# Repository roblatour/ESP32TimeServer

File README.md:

# ESP32 NTP and PTP Stratum 1 Time Server (version 4.0)

An ESP32 NTP and PTP Stratum 1 Time Server for home networks

---

## Overview

This project was born with a simple goal: create a low-budget, **Stratum 1
Network Time Protocol (NTP) time server** with no need for periodic
Linux OS updates. Rather just set it up and let it do its job.

More recently Precision Time Protocol (PTP) support has been added.

ESP32TimeServer can serve NTP, PTP Layer 2 PTP, and PTP Layer 3
UDP Multicast, individually or in any combination.

ESP32TimeServer uses a **GNSS (North America & Europe) receiver** as its time source, 
making it a true Stratum 1 server — meaning it gets its time directly from satellites
rather than from another server. Every device on your home network can then
synchronize to it for highly accurate local time.

ESP32TimeServer supports Waveshare ESP32-P4 Ethernet dev boards and the 
ESP32-S31 Function CoreBoard-1.

---

## What's New

**Version 4** brings the following changes:

- Support for the ESP32-S31 (preview) chip which provides for Gigabit Ethernet.
  Performance of the ESP32-S31 (preview) chip surpasses  the ESP32-P4 rel 1.3 chip,
  but is below the ESP32-P4 rel 3.2 chip. 
- Added Precision Time Protocol (PTP) support. The server can now operate
  as an NTP, PTP Layer 2 (L2), PTP Layer 3 (L3) UDP Multicast, or any and all 
  combinations simultaneously.
- Both the NTP and PTP L2 protocols support operation with or without 
  authentication. NTP and PTP L2 have independent mixed/authenticated-only 
  policy settings, each defaulting to mixed mode. 
  Additional notes: 
  1. PTP servers sync time with their clients with a degree of precision measured in 
  Nanoseconds (ns) as opposed to a Network Time Protocol (NTP) server with a degree of
  precision measured in Microseconds (µs) (1 second = 1 million µs = 1 billion ns).
  2. PTP servers and their followers, will not work in virtual environments nor 
  across router (OPNSense/pfSense) interfaces - they do however work
  within the same interface. 
  3. Linux chrony implementations provides for NTP time and or 
  PTP L2 time with a fall back to NTP time.  Windows implementations
  provide for either NTP time or PTP L3 time but with not
  PTP L3 with NTP fallback.
- added/updated the following companion programs:

  (added) ESP32PTPL2Follower ( https://github.com/roblatour/ESP32PTPL2Follower )
  an example PTP L2 Follower for the ESP32-P4 and ESP32-S31 platforms

  (added) ESP32PTPL3Follower ( https://github.com/roblatour/ESP32PTPL3Follower )
  an example PTP L3 UDP Multicast Follower for the ESP32-P4 and ESP32-S31 platforms
  
  (added) tools\configTimeSettings.ps1 a python script to automate the setup of native
  Windows w32time client for use with ESP32TimeServer in either NTP or PTP L3 UDP modes
    
  (updated) ESP32TimeServerTester ( https://github.com/roblatour/ESP32TimeServerTester )
  to test PTP L2 and L3 UDP Multicast servers 

- removed use of the Arduino Sparkfun GNSS library (adapting its needed code for use within 
  ESP-IDF) as well as the last vestiges of Arduino code.  This was done to support the
  ESP32-S31 chip which while supported in the ESP-IDF environment is 
  not supported in the Arduino environment (although may be in the future)
- added automated regression testing 
  for more information please see [here](./testing/README.md)
- updates to MQTT messaging for new PTP reporting and to provide for, in most cases, more saved 
  messages in memory when a TF card is not available
- updates to Home Assistant configurations for new PTP reporting
- added external TF card reader support for the ESP32-S31 as the Espressif Functional CoreBoard - 1
  does not have a built in TF card reader
- revised leap-second processing aligned to the CGPM's decision to do away with leap-second processing in May 2027 
  for more information please see [here](./misc/leap_second_handling.md)
- added read back confirmation of Ublox receiver going in to stationary mode 
- several other updates and improvements

**Version 3** further improvements:
- **NTPv4 Symmetric-key authentication** added for Windows 
  clients using Meinberg and Linux clients using chrony. 
- **WS2182** RGB LED support added.
- **Stationary GNSS mode** — with UBLOX compliant GNSS receivers the program enables
  stationary-mode for improved time reporting. 
- updated to use Espressif's Ethernet and OTE update (TCP 3232) processes in place of 
  the Arduino Ethernet and OTE update (UDP 3232) processes
- improved accuracy when using the ESP32-P4 release 3.0 or above chip

**Version 2** was a ground-up rewrite which came with a faster, more capable board 
support and a long list of accuracy, reliability, and convenience improvements over
version 1, including:

- **Higher accuracy, lower jitter** — full use of the GPS module's PPS
  (Pulse Per Second) pin disciplines the clock for sub-millisecond accuracy,
  with hardware time stamping and RFC 9769-compatible interleaved responses
  further reducing jitter for both NTPv3 and NTPv4 requests.
- **Faster, more modern hardware** — built around the WaveShare ESP32-P4-ETH
  (or the newer ESP32-P4-WIFI6-ETH), a significant step up from the
  ESP32-WROOM-32/32E used in v1.
- **Broader GNSS module support** — still works great with the recommended
  SparkFun MAX-M10S, but also supports lower-cost generic GNSS modules and now
  has experimental support for the GT-U16, which offers better reception than
  some competing receivers at the same or higher price points.
- **Wired firmware updates** — Over-the-Ethernet updates let you push
  new firmware directly from VS Code, with on-screen progress shown on the
  LCD, so you rarely need to plug in a cable after the first flash.
- **Handles more traffic** — greatly increased throughput and concurrent
  request handling, so the server keeps up even on busy networks.
- **IPv6 support** — the server now responds to NTP requests over IPv6 as
  well as IPv4.
- **Flexible networking** — set a custom MAC address or a static IP, instead
  of always relying on the device's default address and DHCP.
- **MAC address selection** — `MACAddress` is a base-MAC override and is applied
  before Ethernet starts. For PTP master selection, use the active six-byte
  address reported as `Active Ethernet MAC` at startup; the SDK may derive a
  different Ethernet source MAC from the base address.
- **Optional LCD support** — a 4x20 LCD screen was required in v1; 
  in v2 it's entirely optional, along with an optional up time / reset button.
- **Optional KY-016 RGB LED support added** — [here](misc/status_indicators.md)
  is how that is used.
- **Smart GNSS lock tracking** — improved satellite lock and PPS discipline
  tracking, with results correctly reported as Stratum 16 (undefined) if lock
  or discipline is temporarily lost, and automatic recovery once it's
  restored.
- **Quick restarts** — GPS module identity and baud rate are saved to
  non-volatile storage, so the server starts up quickly after the initial
  setup.
- **MQTT publishing** — optionally publish time server stats to an MQTT
  broker, with TF card support for queueing far more messages if the broker
  connection drops.
- **Home Assistant integration** — ready-made entity and dashboard setup
  instructions for pulling time server stats into Home Assistant.
- **Built-in self-test** — an optional startup health check lets the server
  verify its own core functionality every time it boots.
- **Testing tools and guidance** — instructions, tools, and links for
  measuring jitter, drift, RFC 9769 compliance, memory usage, and server
  performance under stress.
- **Updated 3D printed case** — enclosure files refreshed for the new
  WaveShare ESP32-P4-ETH board.

 **Version 1** described in detail [here](https://hackaday.io/project/189309-esp32-ntp-time-server-stratum-1) was built for Arduino / PlatformIO and remains available
 [here](https://github.com/roblatour/ESP32TimeServer/releases/tag/v1.0.0.0).
>
([Detailed release history](https://github.com/roblatour/ESP32TimeServer/releases))

---

## Hardware

| Qty | Item                                                                                                                                                                                                                                                                                                                                                                                                                                                                                                                                                                                                                                                                                                                                                                         |
| --- | ---------------------------------------------------------------------------------------------------------------------------------------------------------------------------------------------------------------------------------------------------------------------------------------------------------------------------------------------------------------------------------------------------------------------------------------------------------------------------------------------------------------------------------------------------------------------------------------------------------------------------------------------------------------------------------------------------------------------------------------------------------------------------- |
| 1   | WaveShare [ESP32-P4-ETH](https://www.waveshare.com/esp32-p4-eth.htm?sku=32086) or [ESP32-P4-WIFI6-ETH](https://www.waveshare.com/esp32-p4-wifi6-poe-eth.htm?sku=32832) development board (with or without optional PoE) <sup>1 2</sup>, or the experimental [ESP32-S31 Function CoreBoard-1](https://www.aliexpress.com/item/1005013174212520.html).                                                                                                                                                                                                                                                                                                                                                                                                                         |
| 1   | GPS/GNSS module Recommened: [SparkFun GNSS Receiver Breakout - MAX-M10S (Qwiic)](https://www.sparkfun.com/sparkfun-gnss-receiver-breakout-max-m10s-qwiic.html?affiliate_code=dW1O7LlPwh&referring_service=link) <sup>2</sup>.  Additionally, one project user reported using this [MAX-M10N board](https://canada.newark.com/mikroelektronika/mikroe-6786/add-on-brd-microbus-compatible/dp/09AN2199) just fine.  Beyond that, support for the [GT U16](https://www.aliexpress.com/item/1005008288311771.html) has been added in version 2.9 - this receiver offers superior reception when coupled with the right antenna (see notes below).  Additionally, while some lower-cost generic modules UBlox compliant receivers are supported, those without a PPS pin are not. |
| 1   | GPS/GNSS antenna with SMA connector ([SparkFun GPS/GNSS Magnetic Mount Antenna - 3m (SMA)](https://www.sparkfun.com/products/14986?affiliate_code=dW1O7LlPwh&referring_service=link)) <sup>2</sup>. Alternatively the GT U16 with an L1/L5 antenna offers superior reception.  However, in my testing I used the [3M SMA W70C](https://www.aliexpress.com/item/1005008421771962.html?spm=a2g0o.order_list.order_list_main.11.7a7f1802GCXbvZ) L1/L2/L5 antenna an [IPEX to SMA adapter](https://s.click.aliexpress.com/e/_c31hthKJ) and got very good results (I have the antenna bundled with the GT U16 (link above) on order and when I get it and test it I will update this page).                                                                                       |
| 1   | _(Optional)_ RGB LED: KY-016 ([AliExpress](https://s.click.aliexpress.com/e/_c3Jceyex)) or WS2812 ([AliExpress](https://s.click.aliexpress.com/e/_c3rjPVub)) with a 470&Omega; resistor and optional lens cap ([AliExpress](https://www.aliexpress.com/item/1005003854908953.html))                                                                                                                                                                                                                                                                                                                                                                                                                                                                                          |
| 1   | _(Optional)_ 4×20 I²C LCD display with HD44780 controller with PCF8574 I²C backpack ([AliExpress](https://www.aliexpress.com/item/1005006829045609.html)) <sup>2</sup>                                                                                                                                                                                                                                                                                                                                                                                                                                                                                                                                                                                                       |
| 1   | _(Optional)_ Momentary push button for displaying up time and triggering a reset ([AliExpress](https://s.click.aliexpress.com/e/_c4UbVuTN)) <sup>2</sup>                                                                                                                                                                                                                                                                                                                                                                                                                                                                                                                                                                                                                     |
| 1   | _(Optional)_ USB C extension cable (with right angle end) ([AliExpress](https://s.click.aliexpress.com/e/_c3C5c6Kx)) <sup>2</sup> + two M3*8                                                                                                                                                                                                                                                                                                                                                                                                                                                                                                                                                                                                                                 |
| 1   | _(Optional)_ TF Card Reader (only needed for the ESP32-S31 Functional Coreboard-1; the WaveShare ESP32-P4-ETH series boards have a built in TF Card Reader) ([AliExpress](https://s.click.aliexpress.com/e/_c34w6E9D))                                                                                                                                                                                                                                                                                                                                                                                                                                                                                                                                                       |
| 1   | _(Optional)_ TF Card, formatted as FAT32, if you're using MQTT and want a larger queue, kept through power loss, should broker communications be down                                                                                                                                                                                                                                                                                                                                                                                                                                                                                                                                                                                                                        |
| —   | Miscellaneous: Ethernet cable, [female dupont connection wires](https://s.click.aliexpress.com/e/_c3UwFX2R), small 4" .1" zip ties, solder <sup>2</sup>                                                                                                                                                                                                                                                                                                                                                                                                                                                                                                                                                                                                                      |
| —   | A PoE-capable switch, PoE injector, **or** USB-C power supply and USB-C cable                                                                                                                                                                                                                                                                                                                                                                                                                                                                                                                                                                                                                                                                                                |

> ⚠️ **WARNING — Do NOT power the ESP32-P4-POE-ETH or the ESP32-P4-WIFI6-POE-ETH
> via both its USB-C connector and a PoE powered Ethernet cable at the same time.**
> Powering from both simultaneously may damage the ESP32-P4-ETH board, PoE switch,
> or device providing USB power. Either power-supply alone is generally sufficient to
> power the board, GNSS module, LCD screen, etc.  However, if after flashing the 
> firmware and a power recycle the LCD screen blinks on and off for several minutes
> before coming online its a good indication a power-supply (USB charger or 
> PoE injector) issue. In this case try a different USB charger or PoE injector, 
> being careful to always use only one power-supply at a time.

<sup>1</sup> See notes in the 'What's New in Version 2' section above.

<sup>2</sup> _(Optional)_ there are 3D Printable Case designed for use
with ESP32-P4_ETH and these specific components (for more information see below).

_(Also Optional)_ To cut down on wiring a PCB can be used. One designed
to work within this project's 3D printed enclosure is available in the
[`PCB`](./PCB) folder. If your interested, please review the `Readme.md` file in
that folder for more information.

### Wiring

#### GPS module → ESP32-P4-ETH _(mandatory)_

| GPS pin | ESP32-P4-ETH pin |
| ------- | ---------------- |
| GND     | GND              |
| VCC     | 3V3              |
| PPS     | GPIO 20          |
| TXD     | GPIO 21 (RX)     |
| RXD     | GPIO 22 (TX)     |

**Pro Tip:** (Optionally) Adding a capacitor between the GNSS module's Vcc and GND power pins,
placed as close as possible to those pins, can improve GNSS power supply stability. Use a
100nf (aka 0.1μf, aka 104) ceramic capacitor, rated at least 50v, 
such as [this one](https://www.aliexpress.com/item/1005004469852680.html).

**Important:**
 
Some GNSS receivers and breakout boards provide a 3.3v PPS (Pulse-Per-Second) output pin
while others provide a 5v PPS output pin.

1. Only connect a 3.3v PPS pin to an ESP32 GPIO pin, never connect a 5v PPS pin to an ESP32 GPIO pin

2. For the wire between the ESP32-P4's GPIO pin and the GNSS Receiver's PPS pin
use as short and as well connect wire as possible; a standard copper Dupont wire
will be fine assuming its gauge is between 24 AWG and 28 AWG

3. The GNSS GND must be connected to the ESP32 GND

Also of note, the above PPS, TX, and RX pin selections were changed in version 2.4 for better
forward and backward compatibility between revisions of the ESP32-P4 chip.
However, if an earlier version of the software has been working fine for you
then you may be able to use the old pin specifications if you want to avoid
rewiring your project. Please see the ESP32TimeServerSettings.h file for more
information.

#### Up time / Reset button → ESP32-P4-ETH _(optional)_

| Button             | ESP32-P4-ETH pin |
| ------------------ | ---------------- |
| One terminal       | GND              |
| The other terminal | GPIO 3           |

#### WS2812 RGB LED _(optional)_

| LCD pin |                     | ESP32-P4-ETH pin |
| ------- | ------------------- | ---------------- |
| GND     |                     | GND              |
| DI      | 470&Omega; resistor | GPIO 4           |
| 5v      |                     | V5 / VBUS        |
> **Important** with the WS2812 a 470&Omega; resistor is require between the DI and GPIO 4 pin

#### KY-016 RGB LED _(optional)_

| LCD pin | ESP32-P4-ETH pin |
| ------- | ---------------- |
| GND     | GND              |
| BLUE    | GPIO 4           |
| GREEN   | GPIO 5           |
| RED     | GPIO 6           |

#### LCD 2004 (HD44780 + PCF8574 I²C backpack) → ESP32-P4-ETH _(optional)_

| LCD pin | ESP32-P4-ETH pin |
| ------- | ---------------- |
| GND     | GND              |
| VCC     | 3V3              |
| SLC/SCL | GPIO 7           |
| SDA     | GPIO 8           |

Refer to the pin definitions in
[`main/ESP32TimeServerSettings.h`](./main/ESP32TimeServerSettings.h).

#### ESP32-S31 Function CoreBoard 1 wiring

The following are GPIO numbers and the board's corresponding J2 header pin numbers,
**Note board silk screen numbering (J2 pins) do not correspond with the GPIO pin numbering**:

| Peripheral connection              | S31 GPIO     | J2 pin       |
| ---------------------------------- | ------------ | ------------ |
| GNSS receiver RX (MCU TX)          | 22           | D2           |
| GNSS receiver TX (MCU RX)          | 21           | D1           |
| GNSS PPS input                     | 20           | D0           |
| LCD SDA                            | 38           | 22           |
| LCD SCL                            | 39           | 21           |
| Uptime/reset button                | 40           | 19           |
| Onboard addressable LED            | 60           | 6            |
| Optional KY-016 blue / green / red | 46 / 47 / 48 | 16 / 13 / 14 |

Use a common ground and **3.3 V** GNSS UART and PPS signals. Keep the PPS wire
short. 
**Only ever connect the LCD to a 3.3v power pin - never 5v.**  

#### Optional external SPI TF card reader (S31)

Use a reader designed for **3.3 V power and 3.3 V SPI signals**, with a FAT32
microSD/TF card. This add-on provides the same persistent MQTT backlog as the
P4's onboard socket; it is not required for time serving. The GNSS, LCD, button,
LED options, Ethernet, and internal PPS loopback retain their existing pins.

| Reader pin | S31 connection |
| ---------- | -------------- |
| 3.3V       | 3V3 power      |
| CS         | GPIO0          |
| MOSI       | GPIO1          |
| CLK        | GPIO2          |
| MISO/MOSO  | GPIO3          |
| GND        | GND            |

`MOSO` is sometimes a misprint for **MISO** (reader output, MCU input);
confirm this in the reader's documentation. 

Keep the connecting wires to the TF Card reader short.

Insert the card before power-on; mounting is attempted once at startup.
An absent, non-FAT32, or unusable card falls back to the existing RAM queue
without formatting the card.

**Power sharing:** J2 pins 35 and 36 are connections to the same 3.3 V rail,
not two independent supplies and not GPIO signal pins. The LCD and TF reader
can share one 3V3 header connection using a suitable power distribution
connector, with common ground, provided the board regulator, supply, and wiring
can handle the total load, including the GNSS and card write-current peaks.
The number of power pins does not establish available current; check the
reader/card and LCD specifications and the board's remaining current budget.
A 100 nF ceramic capacitor plus a suitable bulk capacitor (for example 10–47 uF)
near the reader can help with transients, but cannot compensate for an
undersized supply.

**Do not connect a reader's 3.3V pin to 5V, directly or through a resistor or
resistor divider.** 

---

## 3D Printed Case

A downloadable 3D printable enclosure designed for use the WaveShare
ESP32-P4-ETH (with or without the POE hat) + Sparkfun GPS boards is included in
the [`3D printable case/`](./3D%20printable%20case/) folder. Both `.stl`
(print-ready) and `.f3z` (Fusion 360 editable source) files are provided so you
can tweak the design to suit your needs.

> **Note:** the 3D printable enclosure files also includes the needed models for
> version 1 (used an Olimex ESP32-PoE-ISO Rev. B dev board).

The existing PCB and cases were designed for the Waveshare boards; they are not
claimed to fit the S31 Function CoreBoard.

---

## Software

### Build and development environment

**To build and flash ESP32TimeServer** you will need **Espressif's ESP-IDF v6.1** or above. 
If you don't already have this software installed, just follow the install instructions
directly below:

https://docs.espressif.com/projects/esp-idf/en/stable/esp32/get-started/index.html

which include these links to get it:

[Installation of ESP-IDF and Tools on Windows](https://docs.espressif.com/projects/esp-idf/en/stable/esp32/get-started/windows-setup.html)

[Installation of ESP-IDF and Tools on Linux](https://docs.espressif.com/projects/esp-idf/en/stable/esp32/get-started/linux-setup.html)

[Installation of ESP-IDF and Tools on macOS](https://docs.espressif.com/projects/esp-idf/en/stable/esp32/get-started/macos-setup.html)

If you want to further develop the project, Visual Studio Code with the ESP-IDF extension is recommended.
However, they are not needed to build and flash the project - the instructions for that are below.

Both Visual Studio Code (Community Edition) and the ESP-IDF extension are free to download and use.
Here is where you can find more information about them and get your copies:

- **[Visual Studio Code](https://code.visualstudio.com/)**
- **[Espressif ESP-IDF Extension for VS Code](https://marketplace.visualstudio.com/items?itemName=espressif.esp-idf-extension)**

#### **For Linux users:**
A kind user of this project has shared more detailed environment setup, build and flash instructions specific to Linux (Debian 13) - these can be found [here](./misc/Linux_specific_setup_instructions.md)

### Dependencies

Dependencies are resolved by the ESP-IDF Component Manager from
[`main/idf_component.yml`](./main/idf_component.yml):

- P4: `esp-idf-lib/hd44780` and `esp-idf-lib/pcf8574`.
- S31: `jef-sure/hd44780`, which supports the existing PCF8574 wiring.
- Both: `espressif/mqtt`, `espressif/mdns`, and `espressif/led_strip`.

The initial S31 build used ESP-IDF 6.1.0, `jef-sure/hd44780` 0.1.3,
`espressif/mqtt` 1.1.0, `espressif/mdns` 1.14.1, and
`espressif/led_strip` 3.1.1. Component versions are resolved independently for
each build directory and may change within the declared version constraints.

If PSRAM is enabled but boot initialization is disabled, set
`CONFIG_SPIRAM_BOOT_HW_INIT=y` and
`CONFIG_SPIRAM_PRE_CONFIGURE_MEMORY_PROTECTION=y` for delayed initialization.
The native path follows `CONFIG_SPIRAM_USE_MALLOC` even if the former Arduino
`CONFIG_ARDUINO_ISR_IRAM` option is enabled. This differs from Arduino's
initializer; the optional path has not yet been validated on hardware.

> **Note:** The ESP-IDF Component Manager resolves these dependencies
> dynamically at build time. Each build directory has its own generated
> `dependencies.lock`; it is not a shared cross-target lock.

## Setup

### Setup Step 1 - Download

Create a folder for this project and clone this repository into it. For example:

```cmd
c:
```

```cmd
mkdir c:\temp\ESP32TimeServerProject
```

```cmd
cd \temp\ESP32TimeserverProject
```

```cmd
git clone https://github.com/roblatour/ESP32TimeServer
```

```cmd
cd ESP32TimeServer
```

### Setup Step 2 - Configuration

All user-configurable settings — GPIO pins, GPS options, LCD options, button
support, time zone, etc. — are centralized in:

```plaintext
main/ESP32TimeServerSettings.h
```

Edit this file to match your desired hardware setup before building. The
ESP-IDF target selected by the build profile chooses the P4 or S31 GPIO branch
automatically; no separate board-name string selects the compiler target.
For a UART console, `serialMonitorSpeed` sets its baud rate. USB Serial/JTAG
does not use this value; UART1 is reserved for the GNSS receiver and cannot be
selected as the console.

> **Note:** The settings file indicates whether certain features are enabled.
> These include support for an Uptime/Restart Button, a Liquid Crystal Display,
> MQTT reporting, and Over the Ethernet Updates. Please also note, that if a
> Liquid Crystal Display is **not** connected, `LIQUID_CRYSTAL_DISPLAY_ENABLED`
> **must** be `0` (disabled) or a critical runtime error will occur.

For a PTP-capable retrofit build, see the
[PTP settings](misc/PTP_transports.md).
These are compile-time choices, not MQTT commands. Keep your existing pins,
GNSS, addressing, secrets, display, and native OTE configuration rather than
copying the donor settings file.

### Setup Step 3 - Build

Open a Command Prompt at the repository root and load the ESP-IDF 6.1
environment. The first build downloads the Component Manager dependencies into
`managed_components`.

```cmd
call C:\esp\v6.1\esp-idf\export.bat
```

Connect the board, then identify the chip model and revision:

```cmd
python -m esptool -p COMx chip-id
```

Replace `COMx` with the actual port. Select the model first; an S31 revision
number must not be interpreted as a P4 revision. For ESP32-P4, choose the
matching profile:v

| Chip revision                  | Profile  | Build directory |
| ------------------------------ | -------- | --------------- |
| P4 before v3.0                 | `pre_v3` | `build_pre_v3`  |
| P4 v3.0                        | `v3_0`   | `build_v3_0`    |
| P4 v3.1 or later               | `v3_1`   | `build_v3_1`    |
| ESP32-S31 Function CoreBoard 1 | `s31`    | `build_s31`     |

For example:

```cmd
python .\tools\build.py --profile v3_1
```

Use `--profile v3_0` or `--profile pre_v3` for the other P4 profiles, or
`--profile s31` for the S31. The helper supplies `--preview` for S31. Each
profile keeps its generated `sdkconfig` inside its own build directory. The
helper does not flash, delete the existing root `sdkconfig`, or run
`set-target` on incremental builds. It rejects a build directory configured
for a different target or revision. Use `--build-dir .\my_build` to choose a
different workspace-local directory, `--define NAME=VALUE` to add a CMake
definition, and `--reconfigure` when reconfiguration is intentional.

For an equivalent initial raw v3.1 build, use a fresh directory:

```cmd
idf.py -B .\build_v3_1 ^
  -D IDF_TARGET=esp32p4 ^
  -D SDKCONFIG=.\build_v3_1\sdkconfig ^
  -D "SDKCONFIG_DEFAULTS=sdkconfig.defaults;config\esp32p4_rev_v3_1.defaults" ^
  build
```

For the other revisions, substitute their profile directory, generated
`sdkconfig`, and matching file under `config`. ESP-IDF also applies
`sdkconfig.defaults.esp32p4`, including the P4's 32 MB flash. The equivalent
fresh S31 build is:

```cmd
idf.py --preview -B .\build_s31 ^
  -D IDF_TARGET=esp32s31 ^
  -D SDKCONFIG=.\build_s31\sdkconfig ^
  -D "SDKCONFIG_DEFAULTS=sdkconfig.defaults;config\esp32s31_function_coreboard_1.defaults" ^
  build
```

Preserve existing customized configurations; defaults do not
override options already selected in them. 
Performance optimization must remain explicitly selected in an existing `sdkconfig`.

### Setup Step 4 - Flash

In the same Command Prompt where ESP-IDF 6.1 was loaded:

```cmd
idf.py -B .\build_v3_1 -p COMx flash monitor
```

For S31, use its matching output directory and preview flag:

```cmd
idf.py --preview -B .\build_s31 -p COMx flash monitor
```

> Note: Replace `COMx` with your actual serial port. For example: COM6
>
> Use the directory for the profile you built. Do not use `--force` to flash an
> image to the wrong chip or an earlier ESP32-P4 revision.

On S31, select the port for the board's USB Serial/JTAG or USB-to-UART
connection. Keep programming pins separate from the GNSS UART pins. The
application images are `build_<profile>\ESP32TimeServer.bin`; P4 and S31
images, and images with different P4 revision requirements, are not
interchangeable.

### Over The Ethernet (OTE) Updates

Following the initial flash, OTE updates can be performed if
`OTE_UPDATES_ENABLED` was set to `1` (Enabled) for the initial build and flash.
For more information, please see [`UsefulPowerShellCommands.md`](./misc/UsefullPowerShellCommands.md).
OTE checks the image chip and revision before starting the update. Verify
cross-target and incompatible-revision rejection on the actual device; never
bypass those checks.

---

## Setting up your network / systems to make use of ESP32 Time Server

To make use of ESP32TimeServer on your network /systems please see [`here`](misc/setup.md)

---

## Validating Your Time Server

Once running, and with your Network and System changes setup, you can validate
accuracy at [https://time.is](https://time.is).

This is only a basic connectivity check. Native GNSS, S31 Ethernet and
accessories, NTP/PTP hardware timestamps, and timing accuracy require the
physical acceptance and load measurements listed in
[the S31 plan](./adding_s31_support.md). They remain pending for Phase 2.

You're also welcome to use this open source software (also developed by me) to
stress test your time server:

<https://github.com/roblatour/TimeServerStressTest>

---

## License

This project is released under the **MIT License** — see the [LICENSE](LICENSE)
file for details.

---

## Supporting This Project

To help support this project, or to just say thanks, you're welcome to 'buy me a
coffee'.

---

Copyright © 2026 Rob Latour

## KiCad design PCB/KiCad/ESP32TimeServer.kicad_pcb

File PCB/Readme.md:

# KiCad PCB Files for ESP32 Time Server

This folder and its sub-folders contain the KiCad files used to create the ESP32
Time Server's PCB.

> **Important:**
>
> **This PCB is compatible with a Waveshare ESP32-P4-ETH development board
> (or its POE variant) when the GPIO pin defaults for ESP32TimeServer v2.4
> and beyond are used.**
>
> Special thanks to gitbub user **TMW2N** who updated the PCB files
> in this repository for use with ESP32TimeServer v2.4 and beyond.
> 

The BOM components part numbers needed to order this board via JLCPBC are as
follows:

| Item                           | Qty | JLCPCB Part Number | Url                                                                |
| ------------------------------ | --- | ------------------ | ------------------------------------------------------------------ |
| 20 pin socket for ESP32-P4-ETH | 2   | C2905423           | https://jlcpcb.com/partdetail/3175197-KH_2_54FH_1X20P_H85/C2905423 |
| 8 pin socket for GPS           | 1   | C2905417           | https://jlcpcb.com/partdetail/3175191-KH_2_54FH_1X8P_H85/C2905417  |
| connector for LCD:             | 1   | C566011            | https://jlcpcb.com/partdetail/JST-B4B_PH_K_SGW/C566011             |
| connector for button:          | 1   | C5251182           | https://jlcpcb.com/partdetail/JST-B2B_PH_K_SGW/C5251182            |

Also, when looking at the other photos of the PCB with the components (below)
don't let colour of the wires of the LCD connector cable confuse you. Ideally
they would have been coloured differently. However, I had that pre-wired cable
connector on hand and I just used it.

The pin markings for the external button connector don't matter, as either pin
can be connected to either terminal of the external button.

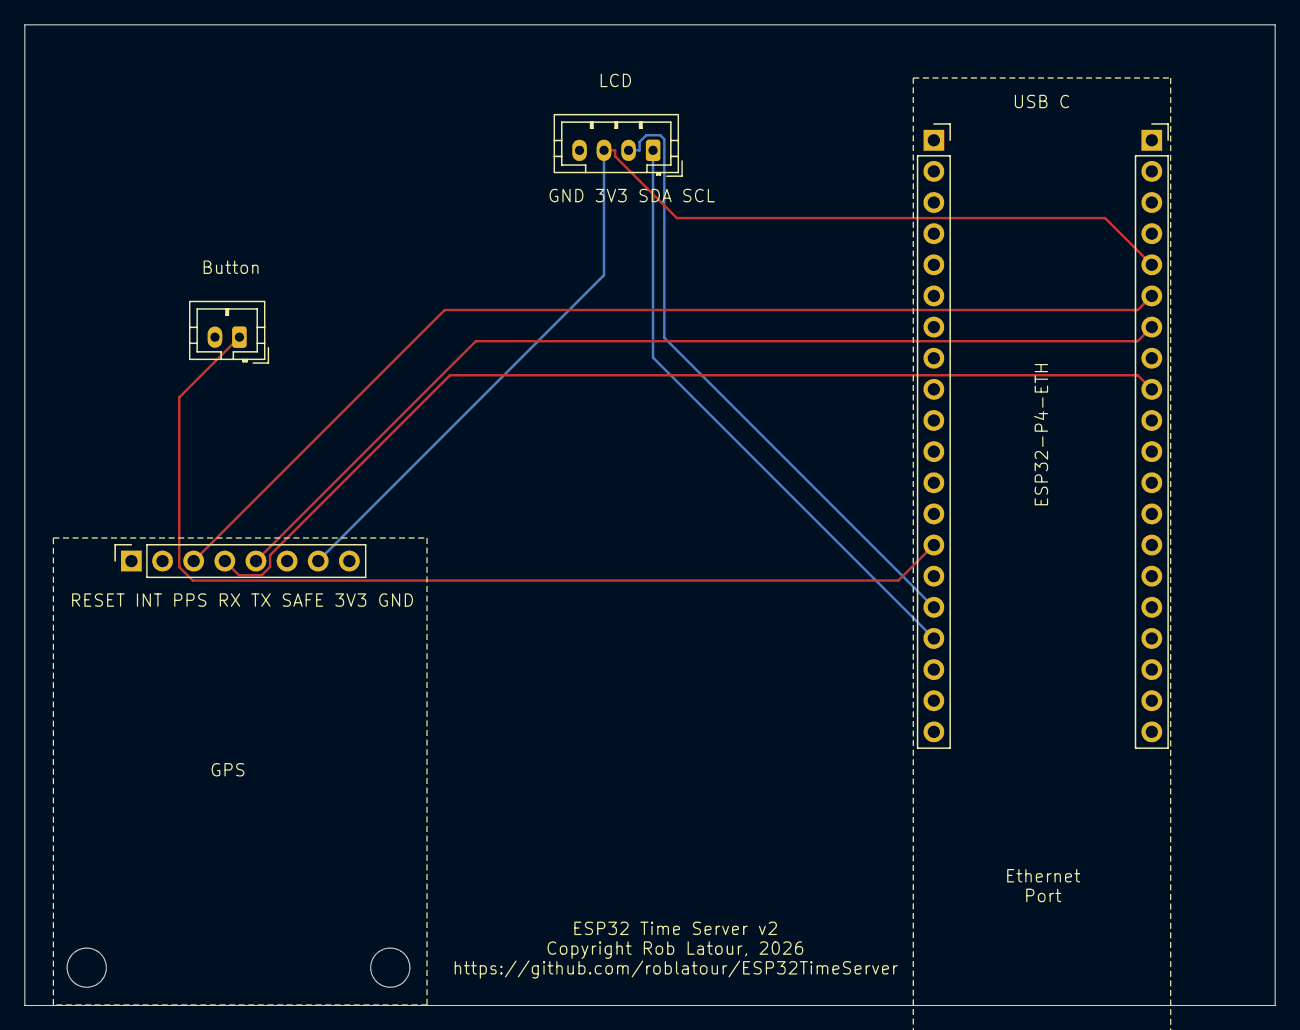
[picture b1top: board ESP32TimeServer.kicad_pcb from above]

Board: 2 copper layers, 102.0 x 80.0 mm, 7 parts (0 on the bottom side), 8 nets.

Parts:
Button1: Conn_01x02; JST_PH_B2B-PH-K_1x02_P2.00mm_Vertical
GPS1: Conn_01x08_Socket; PinSocket_1x08_P2.54mm_Vertical
LCD1: Conn_01x04; JST_PH_B4B-PH-K_1x04_P2.00mm_Vertical
Left1: Conn_01x20_Socket; PinSocket_1x20_P2.54mm_Vertical
REF1, REF2: MountingHole_3.2mm_M3
Right1: Conn_01x20_Socket; PinSocket_1x20_P2.54mm_Vertical

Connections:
+3.3V: GPS1.7, LCD1.3, Right1.5
GND: Button1.2, GPS1.8, LCD1.4, Left1.3, Left1.8, Left1.13, Left1.18, Right1.3, Right1.8, Right1.13, Right1.18
unnamed: Button1.1, Left1.14
unnamed: GPS1.3, Right1.6
unnamed: GPS1.4, Right1.9
unnamed: GPS1.5, Right1.7
unnamed: LCD1.1, Left1.17
unnamed: LCD1.2, Left1.16

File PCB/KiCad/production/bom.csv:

Designator,Footprint,Quantity,Value,LCSC Part #
BUTTON1,JST_PH_B2B-PH-K_1x02_P2.00mm_Vertical,1,Conn_01x02,
GPS1,PinSocket_1x08_P2.54mm_Vertical,1,Conn_01x08_Socket,
LCD1,JST_PH_B4B-PH-K_1x04_P2.00mm_Vertical,1,Conn_01x04,
"LEFT1, RIGHT1",PinSocket_1x20_P2.54mm_Vertical,2,Conn_01x20_Socket,

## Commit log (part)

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2023-01-24 initial release
    ESP32 NTP Stratum 1 Time Server
2023-07-06 minor update
    display UP Time for 10 seconds when button is pressed
2023-08-29 Time Zone setting change now only needed in ESP32TimeServerKeySettings.h file
2023-09-23 Add the current timezone to the clock display
2023-09-25 Add var to enable/disable the time zone display
2023-09-25 Minor update to maintain code consistency
2024-09-06 Update ESP32TimeServer.ino
    updated with comments to clarify various Arduino settings / libraries used
2025-09-02 updates to react to changes in arduino environment
2026-02-06 2026 February 6th update
    - changes for greater long term stability
    - added feature, hold down button for 10 seconds to reboot device
2026-03-23 Fix grammatical errors in README.md
2026-03-23 Fix typos and formatting in README.md
2026-03-23 Update README with version 2 features and clarifications
    Clarify optional components and support for GPS modules in version 2.
2026-03-24 Update README with version 2 features and corrections
    Corrected typos and improved clarity in version 2 features.
2026-03-24 Fix grammar and formatting in README.md
    Corrected grammar and formatting issues in the README.
2026-03-24 Revise version 2 features in README.md
    Updated version 2 features for ESP32 NTP Stratum 1 Time Server in README.
2026-03-24 Fix grammar in version 2 description
    Correct a minor grammatical error in the README.
2026-04-04 Version 2 release
2026-04-04 Fix typo in README regarding OTA updates
2026-04-04 cleanup
2026-04-05 Clarify microcontroller board description in README
    Updated the description of the new microcontroller board for clarity.
2026-04-05 Clarify new microcontroller board details in README
    Updated the description of the new microcontroller board for clarity.
2026-04-05 Fix grammar in Version 2 description
    Corrected grammatical error in the description of the new microcontroller board.

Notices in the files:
README.md:
License:
This project is released under the **MIT License** — see the [LICENSE](LICENSE)
file for details.
License: MIT
Copyright © 2026 Rob Latour
PCB/KiCad/ESP32TimeServer.kicad_pcb:
Copyright Rob Latour, 2026
